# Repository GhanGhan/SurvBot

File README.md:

# SurvBot
Remote controlled robot that surveys the environment it is travelling in.  Designed in KiCad and Altium Designer.

# Part One - Robot Control Unit (RCU)
***Figure 1: Altium Designer 3D View***

***Figure 2: KiCad 3D View***

## Block Diagaram
***Figure 3: SYSTEM BLOCK DIAGRAM (SIMPLE)***

## Project Overview
- Design and implement a PCB that has closed-loop control over 2 DC motors
- Monitors and saves data about itself and the environment it is in:
  - Current flowing though the motors
  - Ambient temperature
  - Ambient light hitting the robot
  - Humidity
  - Orientation (or just the tilt angle, TBD)
- Possess Bluetooth communication
- Entire system is powered by a 9V-12V battery

***Figure 4: SYSTEM OVERVIEW***

## Schematic Diagrams
### Power
***Figure 5: Power Schematic***

- Can be connected to a < 20V at the battery terminals, as well as 5V at either USB connector
- Schottky diodes allow for all three power sources to be connected at once
  - Battery terminal has the highest priority, followed by USB1, then USB2
  - They also provide reverse voltage protection
- Battery can power all of the modules, USB1 and USB2 power all modules except the motor control module
- U100 provides 6V with a maximum output of 3A
- U101 provides 3.3V with a maximum output of 2A
- U102 provides 3.3VA with a maximum output of 1.35A

### Microconroller
***Figure 6: Microconroller Schematic***

- Powered by 3.3V
- Using STM32G0B1CBT6 microcontroller with a clock speed of 16MHz
- Using SWD Interface to program and debug
- Communicates to peripheral ICs using I2C, UART and SPI
- Can use PWM or PH/EN protocol to control motors
- Can connect to a host computer via the USB interface

### Motor Control
***Figure 7: Motor Control Schematic***

- Powered by 6V
- The DRV8876 driver, one for each motor, takes control input signals form microcontroller
- Each motor driver can draw up to 1.5A before shutting down
- Each driver outputs current proportional to the current passing through its associated motor, which is converted to a voltage and sent to a voltage buffer
- Each motor has quadrature encoders, whose signals are fed to the microcontroller

### Bluetooth
***Figure 8: Bluetooth Schematic***

- Powered by 3.3V
- Using ESP32-Mini as a UART-Bluetooth bridge to communicate with a remote controller
- Can be programmed using USB 2.0 via the USB-to-UART IC: CH340C
- By sliding a SPDT switch, can switch between programming mode and communication mode

### Sensors
***Figure 9: Sensors Schematic***

- Powered by 3.3V
- Communicate with microcontroller via I2C interface
- APDS-9306-065: Ambient light sensor, automatically rejects 60Hz flicker
- SHT3D-DIS: Temperature and humidity sensor
- LSM6D53: 6-axis accelerometer and gyroscope

### Current Feedback
***Figure 10: Current Feedback Schematic***

- Powered by 3.3VA
- Takes buffered current-sense output of left and right motor driver as input
  - Signals are filtered to attenuate switching noise before entering the buffer
- Using ADC121C02CIMK to convert analog signal to 12bit digital signal
- Communicates with microcontroller via I2C

### External Memory
***Figure 11: External Memory Schematic***

- Powered by 3.3V
- 32Mb NOR Flash memory
- Communicates with microcontroller via SPI

# Part Two - Remote Controller
***Figure 12: 3D View***

Battery powered hand-held device that controls and monitors the state of the SurvBot. Commands are sent and data is received over Bluetooth. The design includes joysticks to control the robot’s velocity, buttons to change the mode it is in and a screen to display the sensor data. Can be used outdoors or indoors.

## Project Overview
***Figure 13: Remote controller Bloack Diagram***

The user interface will contain joysticks and buttons to control the robot’s velocity and the state it is in.   Such states will determine whether the robot responds to velocity inputs, recording sensor data, is in low power mode etc.  Velocity commands and state changes are sent from the controller to the robot via Bluetooth.  The controller will receive sensor data; encoders, temperature, humidity and motor current from the robot in and display it on the onboard screen in real time.
The system will:
- be powered by a 9V battery
- use 2 thumb joysticks, one to control the robot’s linear velocity and another to control it’s angular velocity
- provide a USB interface to to program the microcontroller
- communicate with the SurvBot over Bluetooth
- provide a screen to view the data from the SurvBot’s motion and environment sensors, and Bluetooth connection status

## Schematic Diagrams
### Power
***Figure 14: Power Schematic***

- Primary power source is a rechargeable 9V battery
- Secondary power source is a USB vable
- Power multiplexing circuitry used to decide the power source
- Power Rails 3.3V and 3V (for the LCD screen)

### Microcontroller
***Figure 7: Microconroller Schematic***

- Programmed via a USB cable whose signals are converted to UART
- Peripherals: ADC, SPI and GPIO
- Has integrated Bluetooth antenna

### User Interface
***Figure 7: User Interface: Screen, Buttons, and Joysticks***

- LCD screen displays information such as state of Bluetooth connection, current speed, temperature, recorded data etc.
- Features 8 buttons to control the state of the robot
- Left joysticks controls rotational speed, right joystick controls linear speed

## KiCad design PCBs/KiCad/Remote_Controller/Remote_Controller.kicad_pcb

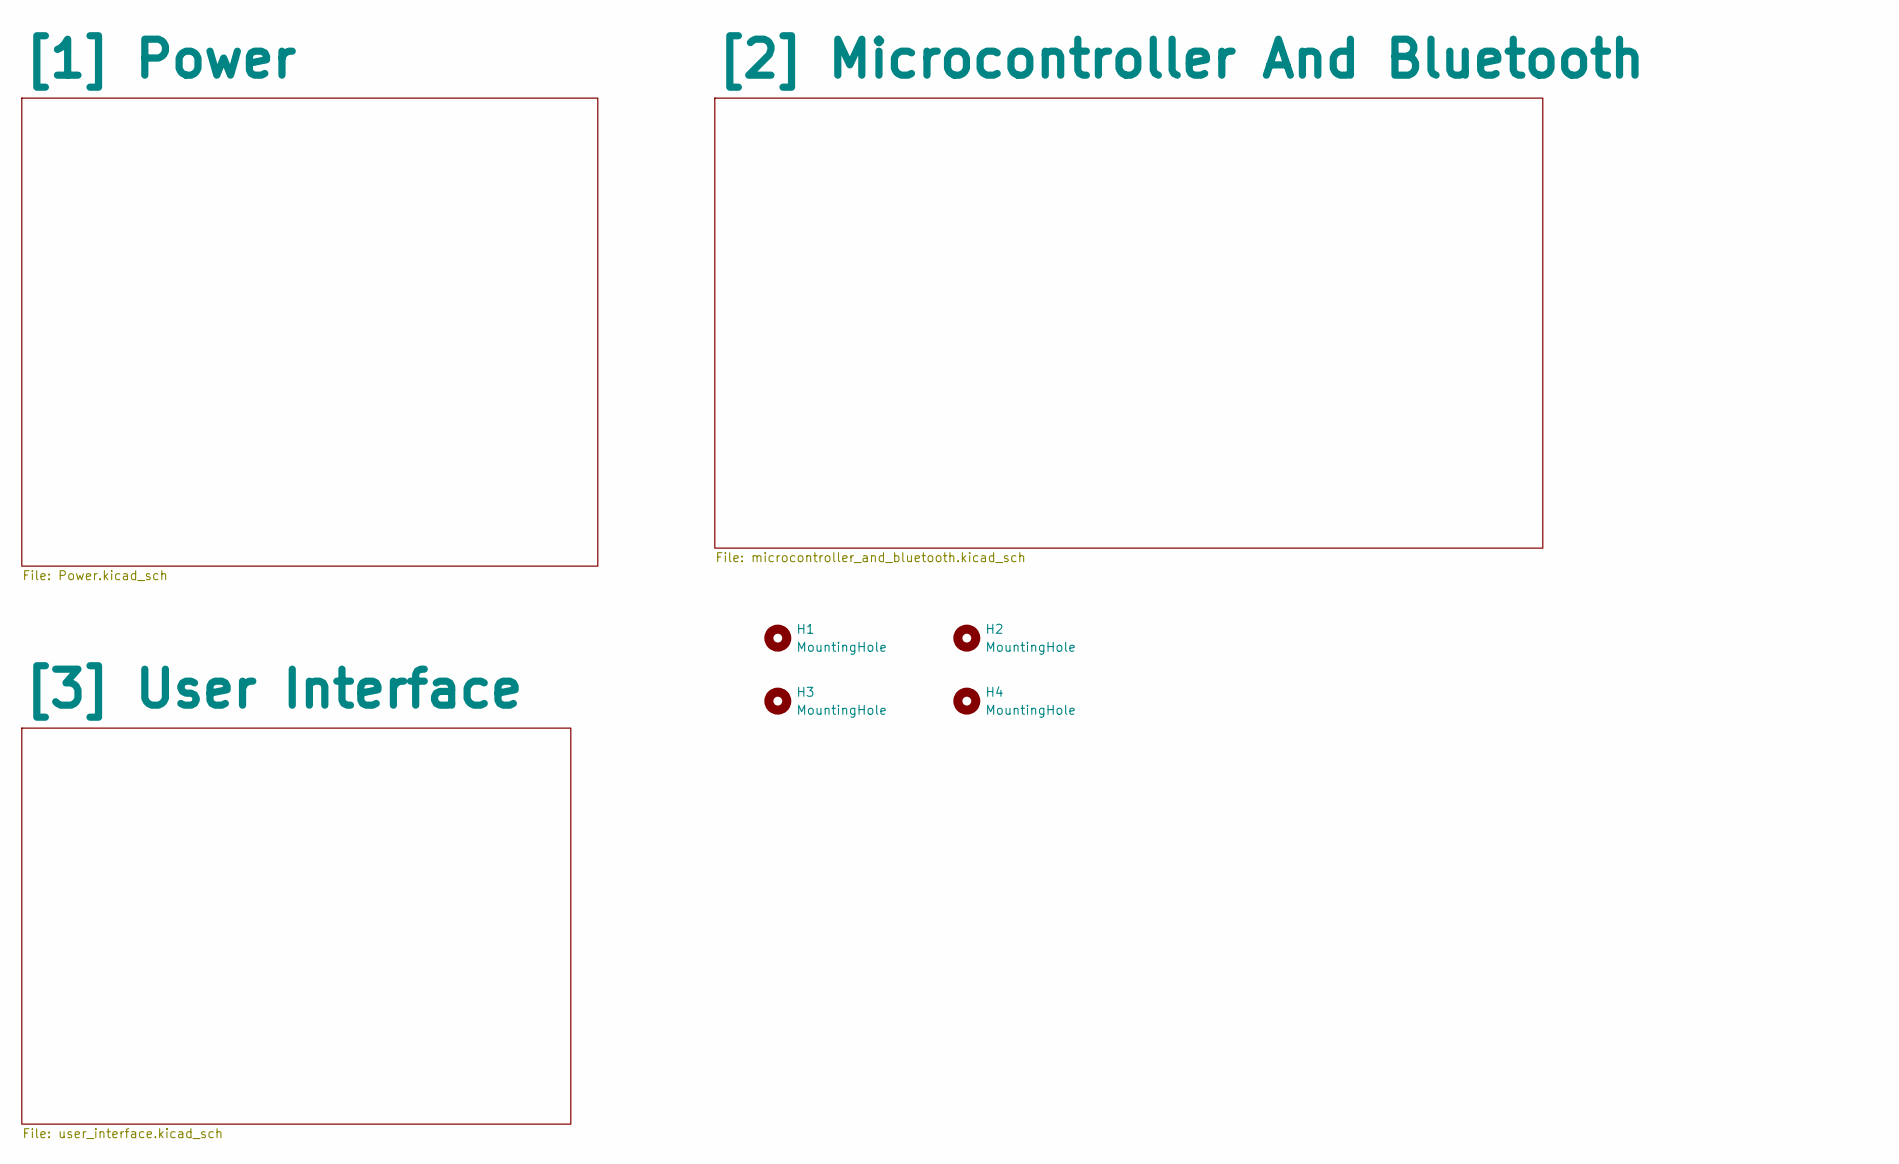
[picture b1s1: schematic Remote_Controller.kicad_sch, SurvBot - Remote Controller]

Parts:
H1, H2, H3, H4: MountingHole; MountingHole_2mm

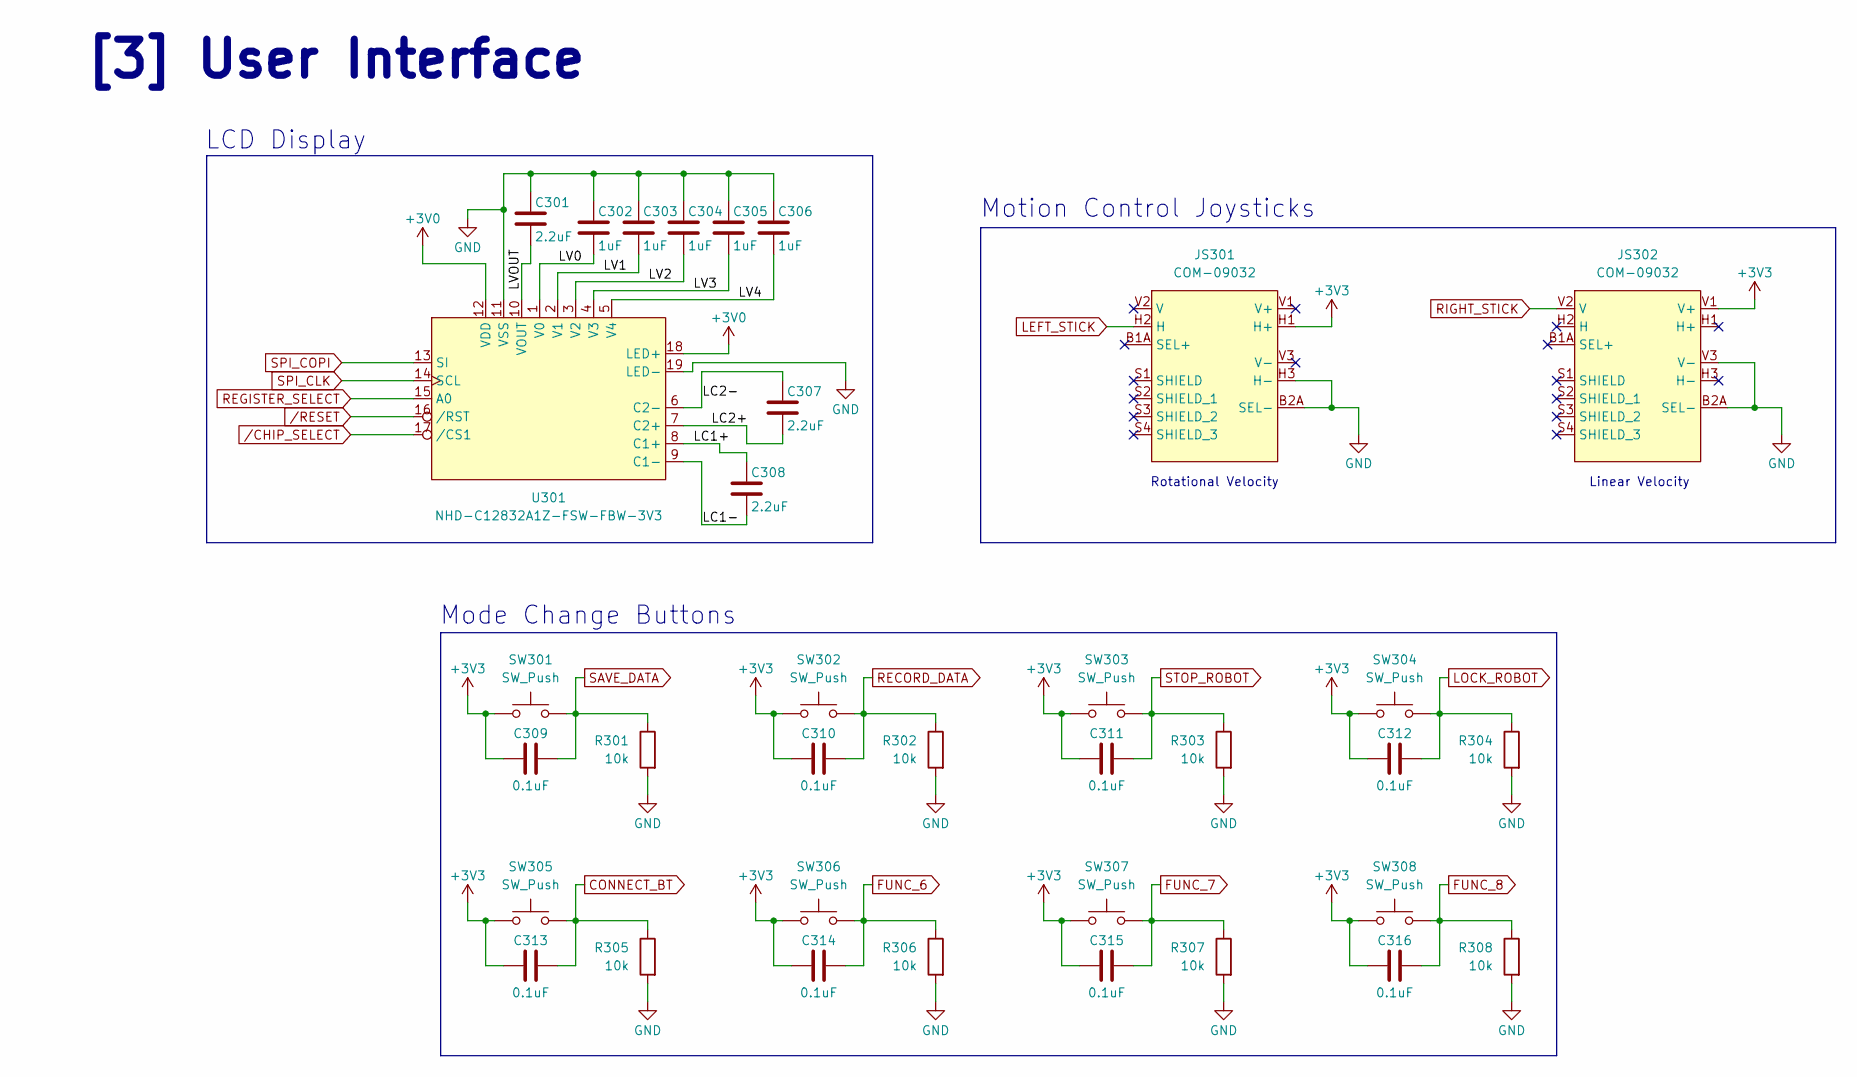
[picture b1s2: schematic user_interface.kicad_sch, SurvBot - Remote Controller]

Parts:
C301, C307, C308: 2.2uF; C_0402_1005Metric; Manufacturer Part # GRM155R61E225ME15D; JLCPCB Part # C72203
C302, C303, C304, C305, C306: 1uF; C_0402_1005Metric; Manufacturer Part # CL05A105KP5NNNC; JLCPCB Part # C14445
C309, C310, C311, C312, C313, C314, C315, C316: 0.1uF; C_0402_1005Metric; Manufacturer Part # CL05B104KA5NNNC; JLCPCB Part # C155422
JS301, JS302: COM-09032; XDCR_COM-09032; Manufacturer Part # COM-09032
R301, R302, R303, R304, R305, R306, R307, R308: 10k; R_0402_1005Metric; Manufacturer Part # 0402WGJ0103TCE; JLCPCB Part # C25531
SW301, SW302, SW303, SW304, SW305, SW306, SW307, SW308: SW_Push; SW_Push_1P1T_NO_CK_PTS125Sx43PSMTR; Manufacturer Part # TS-1003ST-26; JLCPCB Part # C455234
U301: NHD-C12832A1Z-FSW-FBW-3V3; NHD-C12832A1Z-FSRGB; Manufacturer Part # NHD-C12832A1Z-FSW-FBW-3V3

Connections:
+3V0: U301.12 (VDD), U301.18 (LED+); also elsewhere on the board
+3V3: C309.2, C310.2, C311.2, C312.2, C313.2, C314.2, C315.2, C316.2, JS301.H1 (H+), JS302.V1 (V+), SW301.2, SW302.2, SW303.2, SW304.2, SW305.2, SW306.2, SW307.2, SW308.2; also elsewhere on the board
/[3] User Interface/LC1+: C308.1, U301.8 (C1+)
/[3] User Interface/LC1-: C308.2, U301.9 (C1-)
/[3] User Interface/LC2+: C307.2, U301.7 (C2+)
/[3] User Interface/LC2-: C307.1, U301.6 (C2-)
/[3] User Interface/LV0: C302.2, U301.1 (V0)
/[3] User Interface/LV1: C303.2, U301.2 (V1)
/[3] User Interface/LV2: C304.2, U301.3 (V2)
/[3] User Interface/LV3: C305.2, U301.4 (V3)
/[3] User Interface/LV4: C306.2, U301.5 (V4)
/[3] User Interface/LVOUT: C301.2, U301.10 (VOUT)
CONNECT_BT: C313.1, R305.1, SW305.1; also elsewhere on the board
FUNC_6: C314.1, R306.1, SW306.1; also elsewhere on the board
FUNC_7: C315.1, R307.1, SW307.1; also elsewhere on the board
FUNC_8: C316.1, R308.1, SW308.1; also elsewhere on the board
GND: C301.1, C302.1, C303.1, C304.1, C305.1, C306.1, JS301.B2A (SEL-), JS301.H3 (H-), JS302.B2A (SEL-), JS302.V3 (V-), R301.2, R302.2, R303.2, R304.2, R305.2, R306.2, R307.2, R308.2, U301.11 (VSS), U301.19 (LED-); also elsewhere on the board
LEFT_STICK: JS301.H2 (H); also elsewhere on the board
LOCK_ROBOT: C312.1, R304.1, SW304.1; also elsewhere on the board
RECORD_DATA: C310.1, R302.1, SW302.1; also elsewhere on the board
REGISTER_SELECT: U301.15 (A0); also elsewhere on the board
RIGHT_STICK: JS302.V2 (V); also elsewhere on the board
SAVE_DATA: C309.1, R301.1, SW301.1; also elsewhere on the board
SPI_CLK: U301.14 (SCL); also elsewhere on the board
SPI_COPI: U301.13 (SI); also elsewhere on the board
STOP_ROBOT: C311.1, R303.1, SW303.1; also elsewhere on the board
/CHIP_SELECT: U301.17 (/CS1); also elsewhere on the board
/RESET: U301.16 (/RST); also elsewhere on the board

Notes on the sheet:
Mode Change Buttons
LCD Display
Rotational Velocity
Linear Velocity
Motion Control Joysticks
[3] User Interface

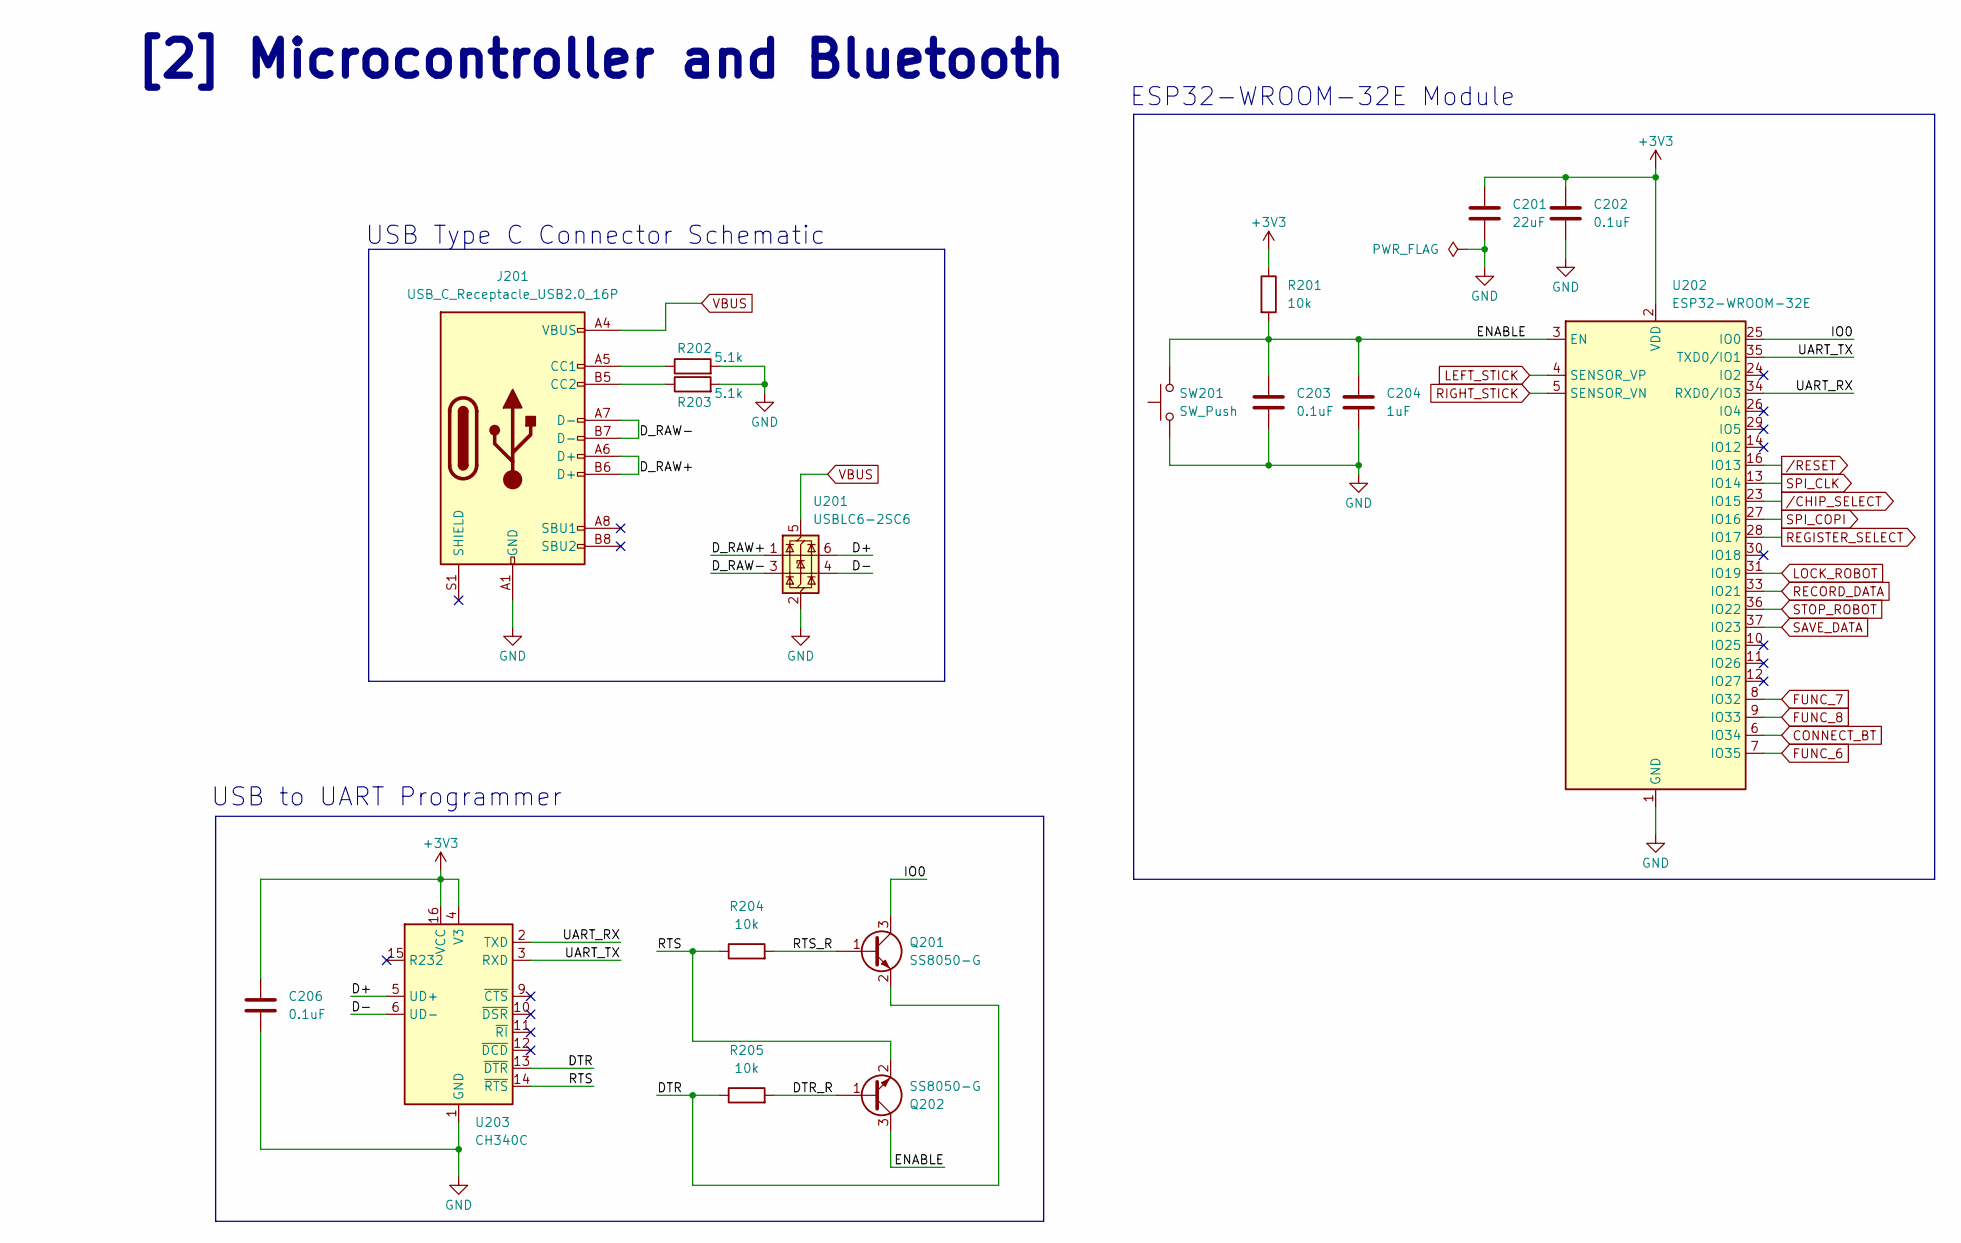
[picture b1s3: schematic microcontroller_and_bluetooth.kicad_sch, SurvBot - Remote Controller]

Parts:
C201: 22uF; C_0603_1608Metric; Manufacturer Part # CL10A226MQ8NRNC; JLCPCB Part # C59461
C202, C203, C206: 0.1uF; C_0402_1005Metric; Manufacturer Part # CL05B104KA5NNNC; JLCPCB Part # C155422
C204: 1uF; C_0402_1005Metric; Manufacturer Part # CL05A105KP5NNNC; JLCPCB Part # C14445
J201: USB_C_Receptacle_USB2.0_16P; USB_C_Receptacle_GCT_USB4105-xx-A_16P_TopMnt_Horizontal; Manufacturer Part # TYPE-C-31-M-12; JLCPCB Part # C165948
Q201, Q202: SS8050-G; SOT-23; Manufacturer Part # SS8050-G; JLCPCB Part # C3199946
R201, R204, R205: 10k; R_0402_1005Metric; Manufacturer Part # 0402WGJ0103TCE; JLCPCB Part # C25531
R202, R203: 5.1k; R_0603_1608Metric; Manufacturer Part # 0603WAF5101T5E; JLCPCB Part # C23186
SW201: SW_Push; SW_Tactile_SPST_NO_Straight_CK_PTS636Sx25SMTRLFS; Manufacturer Part # PTS636SK25SMTRLFS; JLCPCB Part # C2689642
U201: USBLC6-2SC6; SOT-23-6; Manufacturer Part # USBLC6-2SC6; JLCPCB Part # C7519
U202: ESP32-WROOM-32E; ESP32-WROOM-32D; Manufacturer Part # ESP32-WROOM-32E-N4; JLCPCB Part # C701341
U203: CH340C; SOIC-16_3.9x9.9mm_P1.27mm; Manufacturer Part # CH340C; JLCPCB Part # C84681

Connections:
+3V3: C201.1, C202.1, C206.1, R201.1, U202.2 (VDD), U203.4 (V3), U203.16 (VCC); also elsewhere on the board
/[2] Microcontroller And Bluetooth/D+: U201.6 (I/O1), U203.5 (UD+)
/[2] Microcontroller And Bluetooth/D-: U201.4 (I/O2), U203.6 (UD-)
/[2] Microcontroller And Bluetooth/DTR: Q201.2 (E), R205.1, U203.13 (~DTR)
/[2] Microcontroller And Bluetooth/DTR_R: Q202.1 (B), R205.2
/[2] Microcontroller And Bluetooth/D_RAW+: J201.A6 (D+), J201.B6 (D+), U201.1 (I/O1)
/[2] Microcontroller And Bluetooth/D_RAW-: J201.A7 (D-), J201.B7 (D-), U201.3 (I/O2)
/[2] Microcontroller And Bluetooth/ENABLE: C203.1, C204.1, Q202.3 (C), R201.2, SW201.2, U202.3 (EN)
/[2] Microcontroller And Bluetooth/IO0: Q201.3 (C), U202.25 (IO0)
/[2] Microcontroller And Bluetooth/RTS: Q202.2 (E), R204.1, U203.14 (~RTS)
/[2] Microcontroller And Bluetooth/RTS_R: Q201.1 (B), R204.2
/[2] Microcontroller And Bluetooth/UART_RX: U202.34 (RXD0/IO3), U203.2 (TXD)
/[2] Microcontroller And Bluetooth/UART_TX: U202.35 (TXD0/IO1), U203.3 (RXD)
CONNECT_BT: U202.6 (IO34); also elsewhere on the board
FUNC_6: U202.7 (IO35); also elsewhere on the board
FUNC_7: U202.8 (IO32); also elsewhere on the board
FUNC_8: U202.9 (IO33); also elsewhere on the board
GND: C201.2, C202.2, C203.2, C204.2, C206.2, J201.A1 (GND), J201.A12 (GND), J201.B1 (GND), J201.B12 (GND), R202.2, R203.2, SW201.1, U201.2 (GND), U202.1 (GND), U202.15 (GND), U202.38 (GND), U202.39 (GND), U203.1 (GND); also elsewhere on the board
LEFT_STICK: U202.4 (SENSOR_VP); also elsewhere on the board
LOCK_ROBOT: U202.31 (IO19); also elsewhere on the board
unnamed: J201.A5 (CC1), R202.1
unnamed: J201.B5 (CC2), R203.1
RECORD_DATA: U202.33 (IO21); also elsewhere on the board
REGISTER_SELECT: U202.28 (IO17); also elsewhere on the board
RIGHT_STICK: U202.5 (SENSOR_VN); also elsewhere on the board
SAVE_DATA: U202.37 (IO23); also elsewhere on the board
SPI_CLK: U202.13 (IO14); also elsewhere on the board
SPI_COPI: U202.27 (IO16); also elsewhere on the board
STOP_ROBOT: U202.36 (IO22); also elsewhere on the board
VBUS: J201.A4 (VBUS), J201.A9 (VBUS), J201.B4 (VBUS), J201.B9 (VBUS), U201.5 (VBUS); also elsewhere on the board
/CHIP_SELECT: U202.23 (IO15); also elsewhere on the board
/RESET: U202.16 (IO13); also elsewhere on the board

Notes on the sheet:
ESP32-WROOM-32E Module
[2] Microcontroller and Bluetooth
USB to UART Programmer
USB Type C Connector Schematic

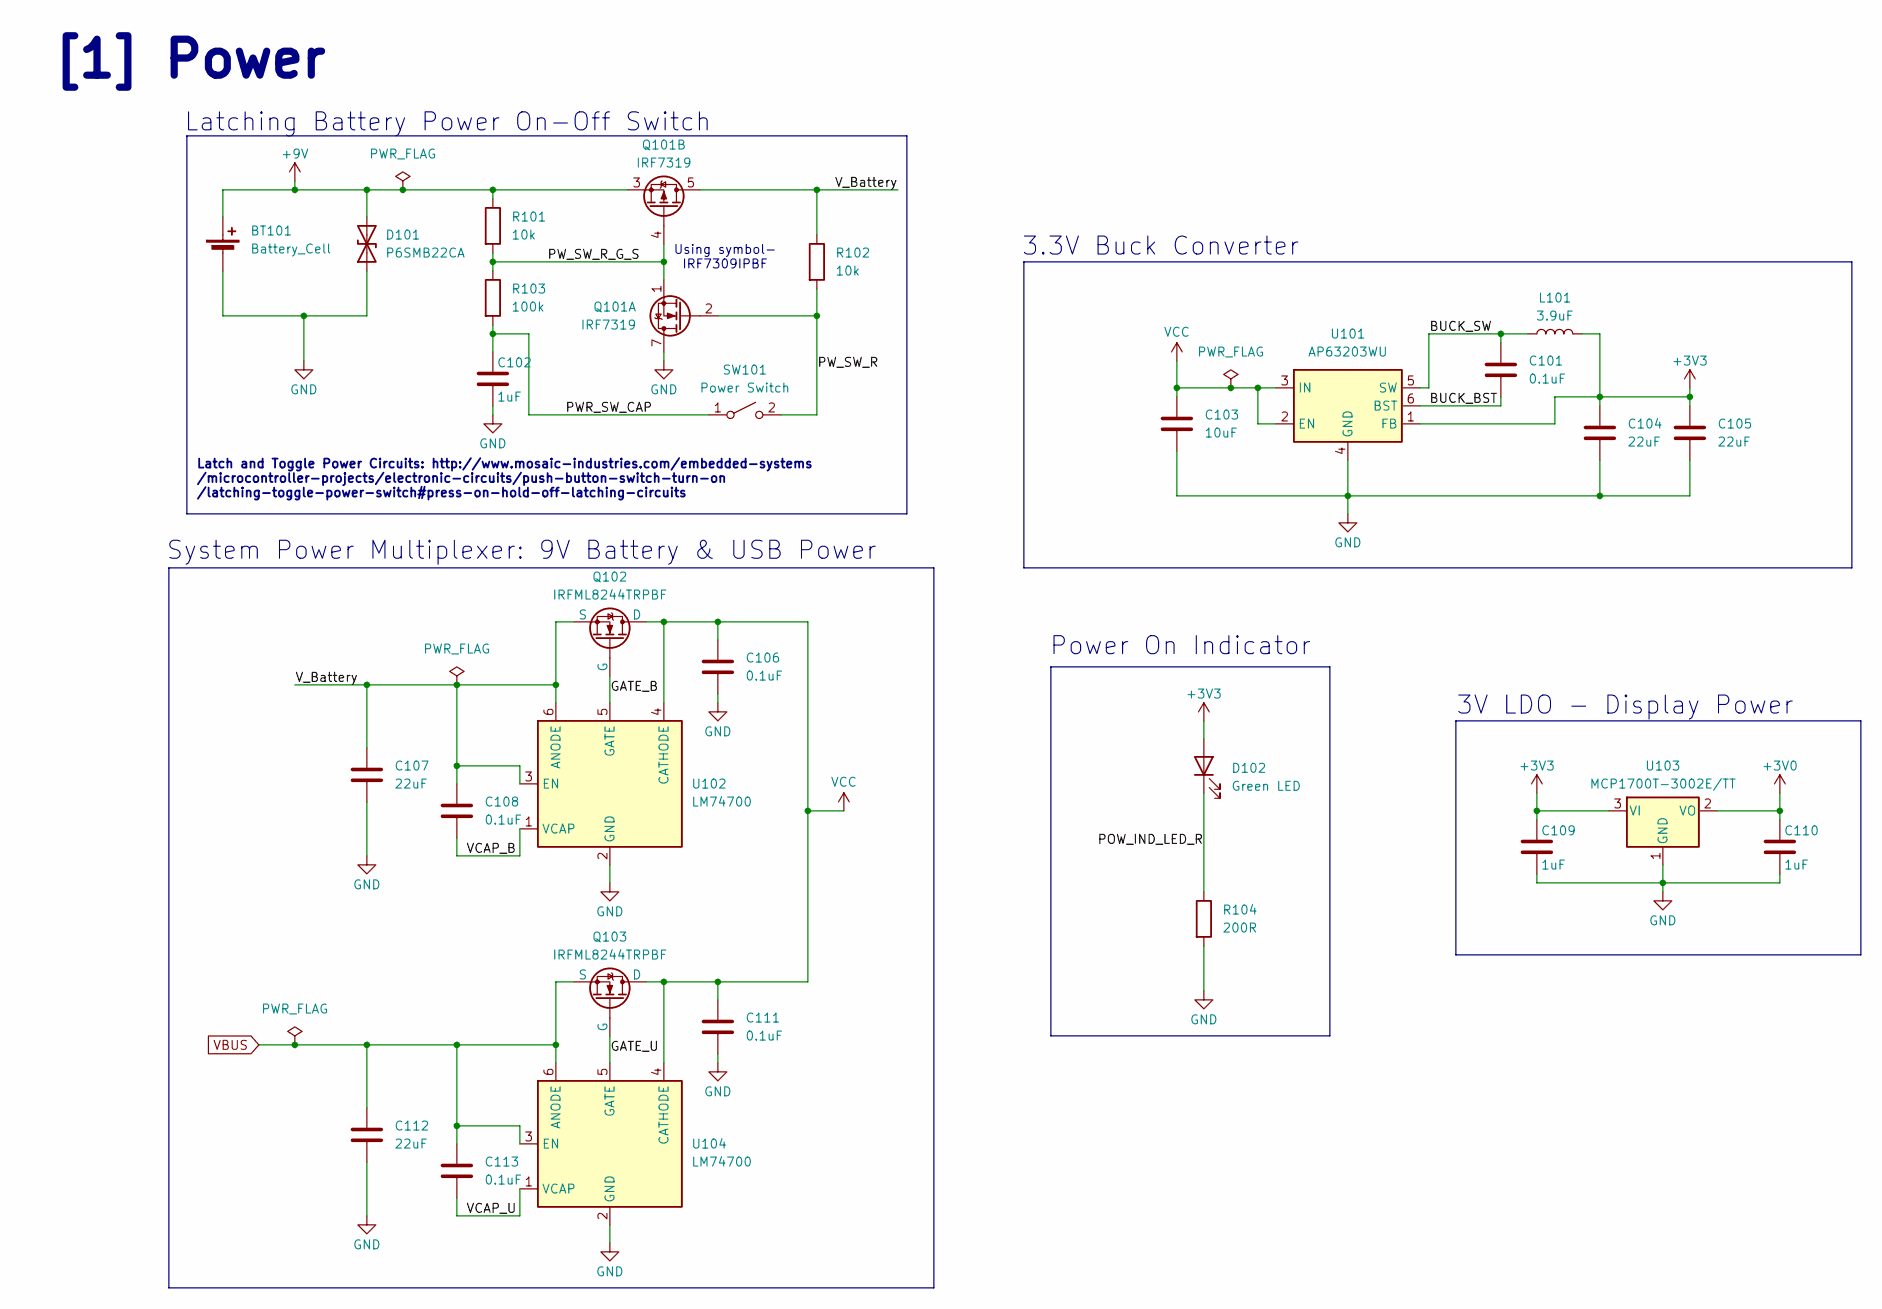
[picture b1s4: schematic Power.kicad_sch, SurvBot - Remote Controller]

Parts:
BT101: Battery_Cell; BatteryHolder_MPD_BA9VPC_1xPP3; Manufacturer Part # BA9VPC
C101, C106, C108, C111, C113: 0.1uF; C_0402_1005Metric; Manufacturer Part # CL05B104KA5NNNC; JLCPCB Part # C155422
C102, C109, C110: 1uF; C_0402_1005Metric; Manufacturer Part # CL05A105KP5NNNC; JLCPCB Part # C14445
C103: 10uF; C_0805_2012Metric; Manufacturer Part # GRM21BR61E106KA73L; JLCPCB Part # C84416
C104, C105, C107, C112: 22uF; C_1206_3216Metric; Manufacturer Part # GRM31CR61E226KE15L; JLCPCB Part # C77091
D101: P6SMB22CA; D_SOD-882; Manufacturer Part # P6SMB22CA; JLCPCB Part # C320520
D102: Green LED; LED_0603_1608Metric; Manufacturer Part # 150060GS75000; JLCPCB Part # C5252984
L101: 3.9uF; L_Vishay_IHLP-2525; Manufacturer Part # SQH6012S-4R0N-LF; JLCPCB Part # C257229
Q101: IRF7319; SOIC-8_3.9x4.9mm_P1.27mm; Manufacturer Part # IRF7319TRPBF; JLCPCB Part # C2760082
Q102, Q103: IRFML8244TRPBF; SOT-23; Manufacturer Part # IRFML8244TRPBF; JLCPCB Part # C5381404
R101, R102: 10k; R_0402_1005Metric; Manufacturer Part # 0402WGJ0103TCE; JLCPCB Part # C25531
R103: 100k; R_0603_1608Metric; Manufacturer Part # RC0603FR-07100KL; JLCPCB Part # C14675
R104: 200R; R_0603_1608Metric; Manufacturer Part # 0603WAF2000T5E; JLCPCB Part # C8218
SW101: Power Switch; SW_Push_1P1T_NO_CK_PTS125Sx43PSMTR; Manufacturer Part # TS-1003ST-26; JLCPCB Part # C455234
U101: AP63203WU; TSOT-23-6; Manufacturer Part # C780769; JLCPCB Part # AP63203WU-7
U102, U104: LM74700; SOT-23-6; Manufacturer Part # LM74700QDBVRQ1; JLCPCB Part # C2941042
U103: MCP1700T-3002E/TT; SOT-23; Manufacturer Part # MCP1700T-3002E/TT; JLCPCB Part # C62244

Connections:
+3V0: C110.1, U103.2 (VO); also elsewhere on the board
+3V3: C104.1, C105.1, C109.1, D102.2 (A), L101.2, U101.1 (FB), U103.3 (VI); also elsewhere on the board
+9V: BT101.1 (+), D101.2 (A2), Q101.3 (1), R101.1
/[1] Power/BUCK_BST: C101.2, U101.6 (BST)
/[1] Power/BUCK_SW: C101.1, L101.1, U101.5 (SW)
/[1] Power/GATE_B: Q102.1 (G), U102.5 (GATE)
/[1] Power/GATE_U: Q103.1 (G), U104.5 (GATE)
/[1] Power/POW_IND_LED_R: D102.1 (K), R104.1
/[1] Power/PWR_SW_CAP: C102.1, R103.2, SW101.1 (A)
/[1] Power/PW_SW_R: Q101.2 (G), R102.2, SW101.2 (B)
/[1] Power/PW_SW_R_G_S: Q101.1 (S), Q101.4 (G), R101.2, R103.1
/[1] Power/VCAP_B: C108.2, U102.1 (VCAP)
/[1] Power/VCAP_U: C113.2, U104.1 (VCAP)
/[1] Power/V_Battery: C107.1, C108.1, Q101.5 (D), Q101.6 (D), Q102.2 (S), R102.1, U102.3 (EN), U102.6 (ANODE)
GND: BT101.2 (-), C102.2, C103.2, C104.2, C105.2, C106.2, C107.2, C109.2, C110.2, C111.2, C112.2, D101.1 (A1), Q101.7 (D), Q101.8 (D), R104.2, U101.4 (GND), U102.2 (GND), U103.1 (GND), U104.2 (GND); also elsewhere on the board
VBUS: C112.1, C113.1, Q103.2 (S), U104.3 (EN), U104.6 (ANODE); also elsewhere on the board
VCC: C103.1, C106.1, C111.1, Q102.3 (D), Q103.3 (D), U101.2 (EN), U101.3 (IN), U102.4 (CATHODE), U104.4 (CATHODE)

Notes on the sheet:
[1] Power
Latching Battery Power On-Off Switch
3.3V Buck Converter
Power On Indicator
3V LDO - Display Power
Using symbol- IRF7309IPBF
System Power Multiplexer: 9V Battery & USB Power
Latch and Toggle Power Circuits: http://www.mosaic-industries.com/embedded-systems /microcontroller-projects/electronic-circuits/push-button-switch-turn-on /latching-toggle-power-switch#press-on-hold-off-latching-circuits

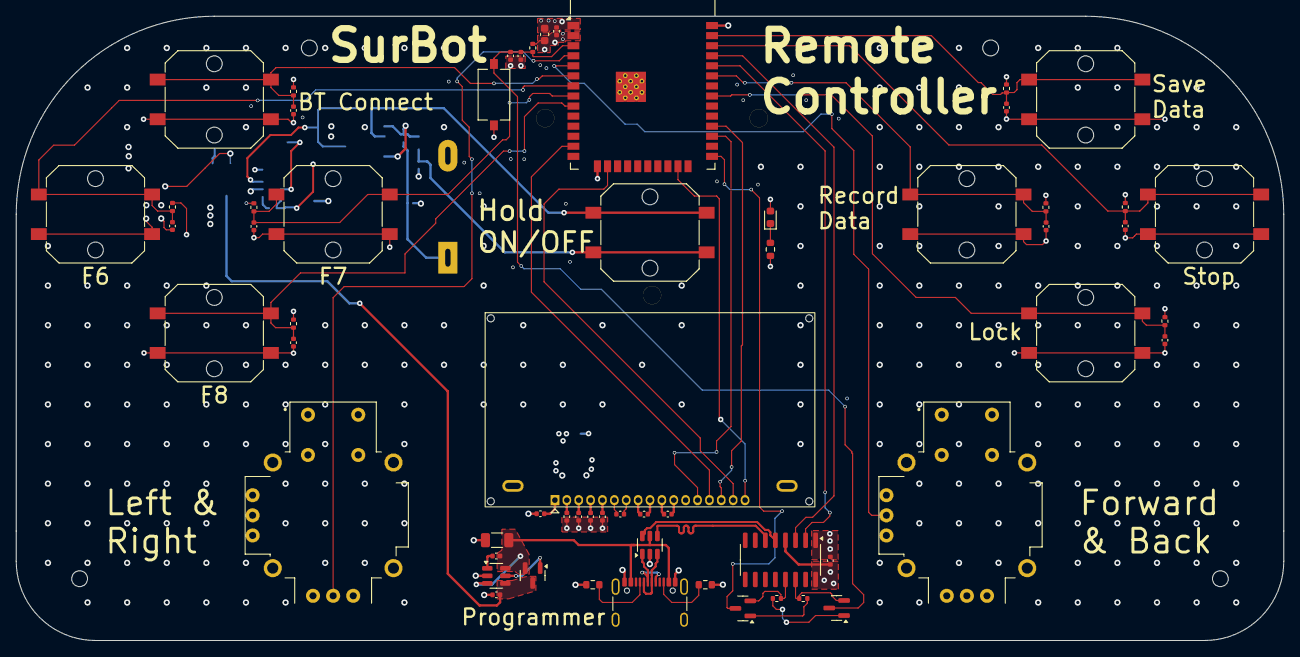
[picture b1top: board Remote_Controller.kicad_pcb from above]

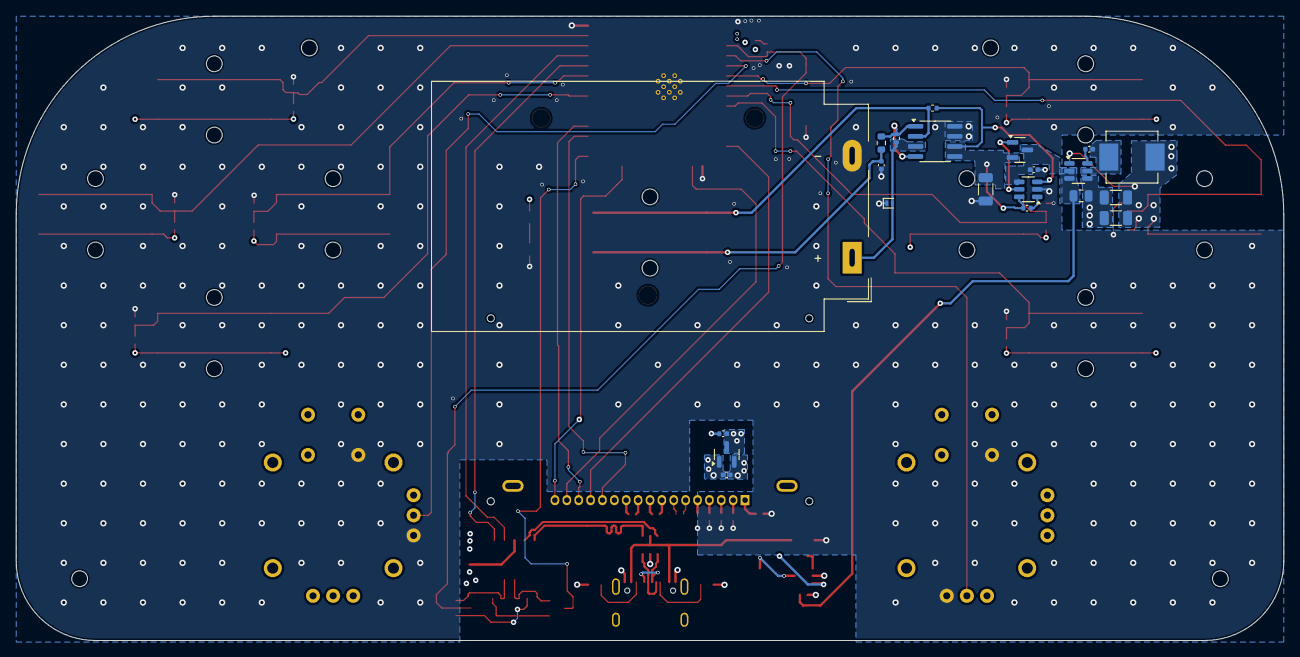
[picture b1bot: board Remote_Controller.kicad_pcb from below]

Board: 4 copper layers, 160.0 x 78.8 mm, 85 parts (21 on the bottom side), 56 nets.

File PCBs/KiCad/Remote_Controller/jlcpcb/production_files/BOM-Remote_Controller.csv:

Comment,Designator,Footprint,LCSC,Quantity
1uF,"C102,C109,C110,C204,C302,C303,C304,C305,C306",C_0402_1005Metric,C14445,9
100k,R103,R_0603_1608Metric,C14675,1
0.1uF,"C101,C106,C108,C111,C113,C202,C203,C206,C309,C310,C311,C312,C313,C314,C315,C316",C_0402_1005Metric,C155422,16
USB_C_Receptacle_USB2.0_16P,J201,USB_C_Receptacle_GCT_USB4105-xx-A_16P_TopMnt_Horizontal,C165948,1
5.1k,"R202,R203",R_0603_1608Metric,C23186,2
10k,"R101,R102,R201,R204,R205,R301,R302,R303,R304,R305,R306,R307,R308",R_0402_1005Metric,C25531,13
3.9uF,L101,L_Vishay_IHLP-2525,C257229,1
SW_Push,SW201,SW_Tactile_SPST_NO_Straight_CK_PTS636Sx25SMTRLFS,C2689642,1
IRF7319,Q101,SOIC-8_3.9x4.9mm_P1.27mm,C2760082,1
LM74700,"U102,U104",SOT-23-6,C2941042,2
SS8050-G,"Q201,Q202",SOT-23,C3199946,2
P6SMB22CA,D101,D_SOD-882,C320520,1
Power Switch,"SW101,SW301,SW302,SW303,SW304,SW305,SW306,SW307,SW308",SW_Push_1P1T_NO_CK_PTS125Sx43PSMTR,C455234,9
Green LED,D102,LED_0603_1608Metric,C5252984,1
IRFML8244TRPBF,"Q102,Q103",SOT-23,C5381404,2
22uF,C201,C_0603_1608Metric,C59461,1
MCP1700T-3002E/TT,U103,SOT-23,C62244,1
ESP32-WROOM-32E,U202,ESP32-WROOM-32D,C701341,1
2.2uF,"C301,C307,C308",C_0402_1005Metric,C72203,3
USBLC6-2SC6,U201,SOT-23-6,C7519,1
22uF,"C104,C105,C107,C112",C_1206_3216Metric,C77091,4
AP63203WU,U101,TSOT-23-6,C780769,1
200R,R104,R_0603_1608Metric,C8218,1
10uF,C103,C_0805_2012Metric,C84416,1
CH340C,U203,SOIC-16_3.9x9.9mm_P1.27mm,C84681,1

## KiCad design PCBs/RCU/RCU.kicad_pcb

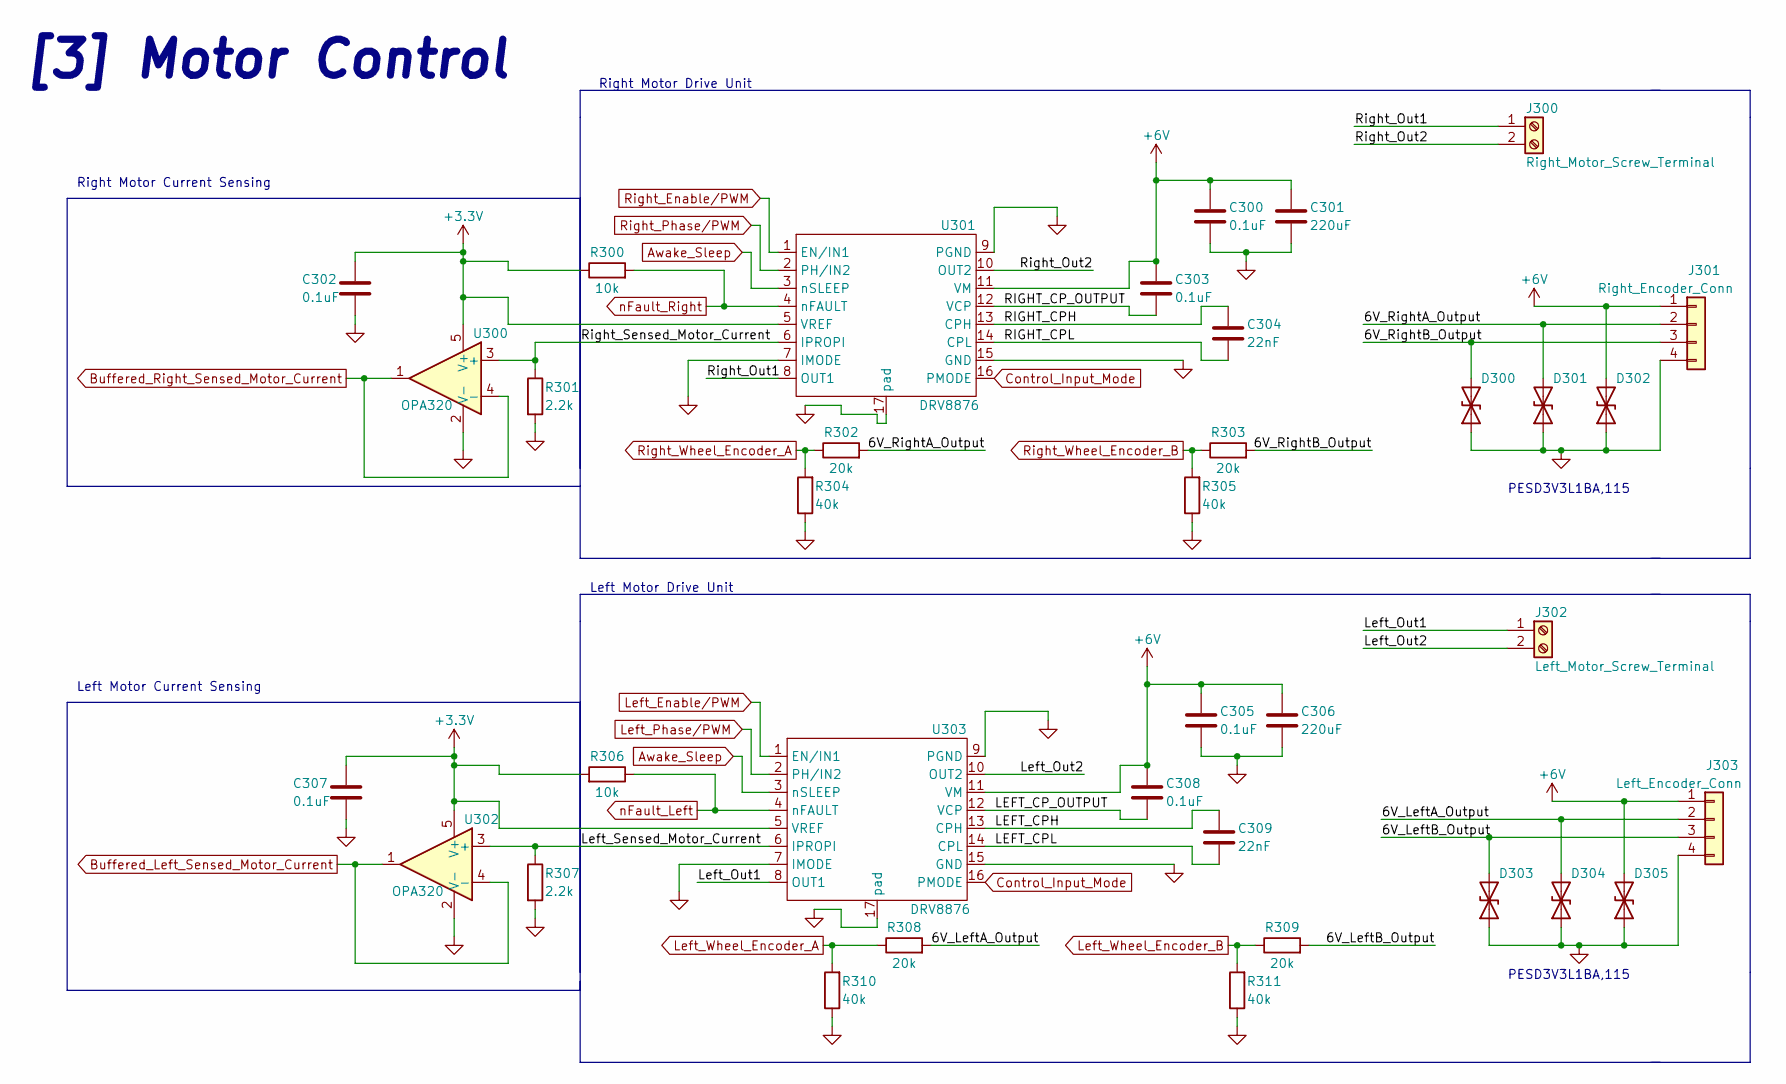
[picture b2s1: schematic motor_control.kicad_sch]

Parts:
C300, C302, C303, C305, C307, C308: 0.1uF; C_0603_1608Metric
C301, C306: 220uF; CP_Radial_D5.0mm_P2.50mm
C304, C309: 22nF; C_0603_1608Metric
D300, D301, D302, D303, D304, D305: PESD3V3L1BA,115; D_SOD-323
J300: Right_Motor_Screw_Terminal; TerminalBlock_bornier-2_P5.08mm
J301: Right_Encoder_Conn; PinHeader_1x04_P2.54mm_Vertical
J302: Left_Motor_Screw_Terminal; TerminalBlock_bornier-2_P5.08mm
J303: Left_Encoder_Conn; PinHeader_1x04_P2.54mm_Vertical
R300, R306: 10k; R_0402_1005Metric
R301, R307: 2.2k; R_0603_1608Metric
R302, R303, R308, R309: 20k; R_0603_1608Metric
R304, R305, R310, R311: 40k; R_0603_1608Metric
U300, U302: OPA320; SOT-23-5
U301, U303: DRV8876; HTSSOP-16-1EP_4.4x5mm_P0.65mm_EP3.4x5mm_Mask2.46x2.31mm_The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

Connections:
+3V3: C302.1, C307.1, R300.1, R306.2, U300.5 (V+), U301.5 (VREF), U302.5 (V+), U303.5 (VREF); also elsewhere on the board
+6V: C300.1, C301.1, C303.1, C305.1, C306.1, C308.1, D302.2 (A2), D305.2 (A2), J301.1, J303.1, U301.11 (VM), U303.11 (VM); also elsewhere on the board
/[3] Motor_Control/6V_LeftA_Output: D304.2 (A2), J303.2, R308.2
/[3] Motor_Control/6V_LeftB_Output: D303.2 (A2), J303.3, R309.2
/[3] Motor_Control/6V_RightA_Output: D301.2 (A2), J301.2, R302.2
/[3] Motor_Control/6V_RightB_Output: D300.2 (A2), J301.3, R303.2
/[3] Motor_Control/LEFT_CPH: C309.1, U303.13 (CPH)
/[3] Motor_Control/LEFT_CPL: C309.2, U303.14 (CPL)
/[3] Motor_Control/LEFT_CP_OUTPUT: C308.2, U303.12 (VCP)
/[3] Motor_Control/Left_Out1: J302.1, U303.8 (OUT1)
/[3] Motor_Control/Left_Out2: J302.2, U303.10 (OUT2)
/[3] Motor_Control/Left_Sensed_Motor_Current: R307.1, U302.3 (+), U303.6 (IPROPI)
/[3] Motor_Control/RIGHT_CPH: C304.1, U301.13 (CPH)
/[3] Motor_Control/RIGHT_CPL: C304.2, U301.14 (CPL)
/[3] Motor_Control/RIGHT_CP_OUTPUT: C303.2, U301.12 (VCP)
/[3] Motor_Control/Right_Out1: J300.1, U301.8 (OUT1)
/[3] Motor_Control/Right_Out2: J300.2, U301.10 (OUT2)
/[3] Motor_Control/Right_Sensed_Motor_Current: R301.1, U300.3 (+), U301.6 (IPROPI)
Awake_Sleep: U301.3 (nSLEEP), U303.3 (nSLEEP); also elsewhere on the board
Buffered_Left_Sensed_Motor_Current: U302.1, U302.4 (-); also elsewhere on the board
Buffered_Right_Sensed_Motor_Current: U300.1, U300.4 (-); also elsewhere on the board
Control_Input_Mode: U301.16 (PMODE), U303.16 (PMODE); also elsewhere on the board
Left_Enable/PWM: U303.1 (EN/IN1); also elsewhere on the board
Left_Phase/PWM: U303.2 (PH/IN2); also elsewhere on the board
Left_Wheel_Encoder_A: R308.1, R310.2; also elsewhere on the board
Left_Wheel_Encoder_B: R309.1, R311.2; also elsewhere on the board
Right_Enable/PWM: U301.1 (EN/IN1); also elsewhere on the board
Right_Phase/PWM: U301.2 (PH/IN2); also elsewhere on the board
Right_Wheel_Encoder_A: R302.1, R304.2; also elsewhere on the board
Right_Wheel_Encoder_B: R303.1, R305.2; also elsewhere on the board
nFault_Left: R306.1, U303.4 (nFAULT); also elsewhere on the board
nFault_Right: R300.2, U301.4 (nFAULT); also elsewhere on the board

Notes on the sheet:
PESD3V3L1BA,115
Left Motor Drive Unit
Right Motor Current Sensing
Right Motor Drive Unit
[3] Motor Control
Left Motor Current Sensing
